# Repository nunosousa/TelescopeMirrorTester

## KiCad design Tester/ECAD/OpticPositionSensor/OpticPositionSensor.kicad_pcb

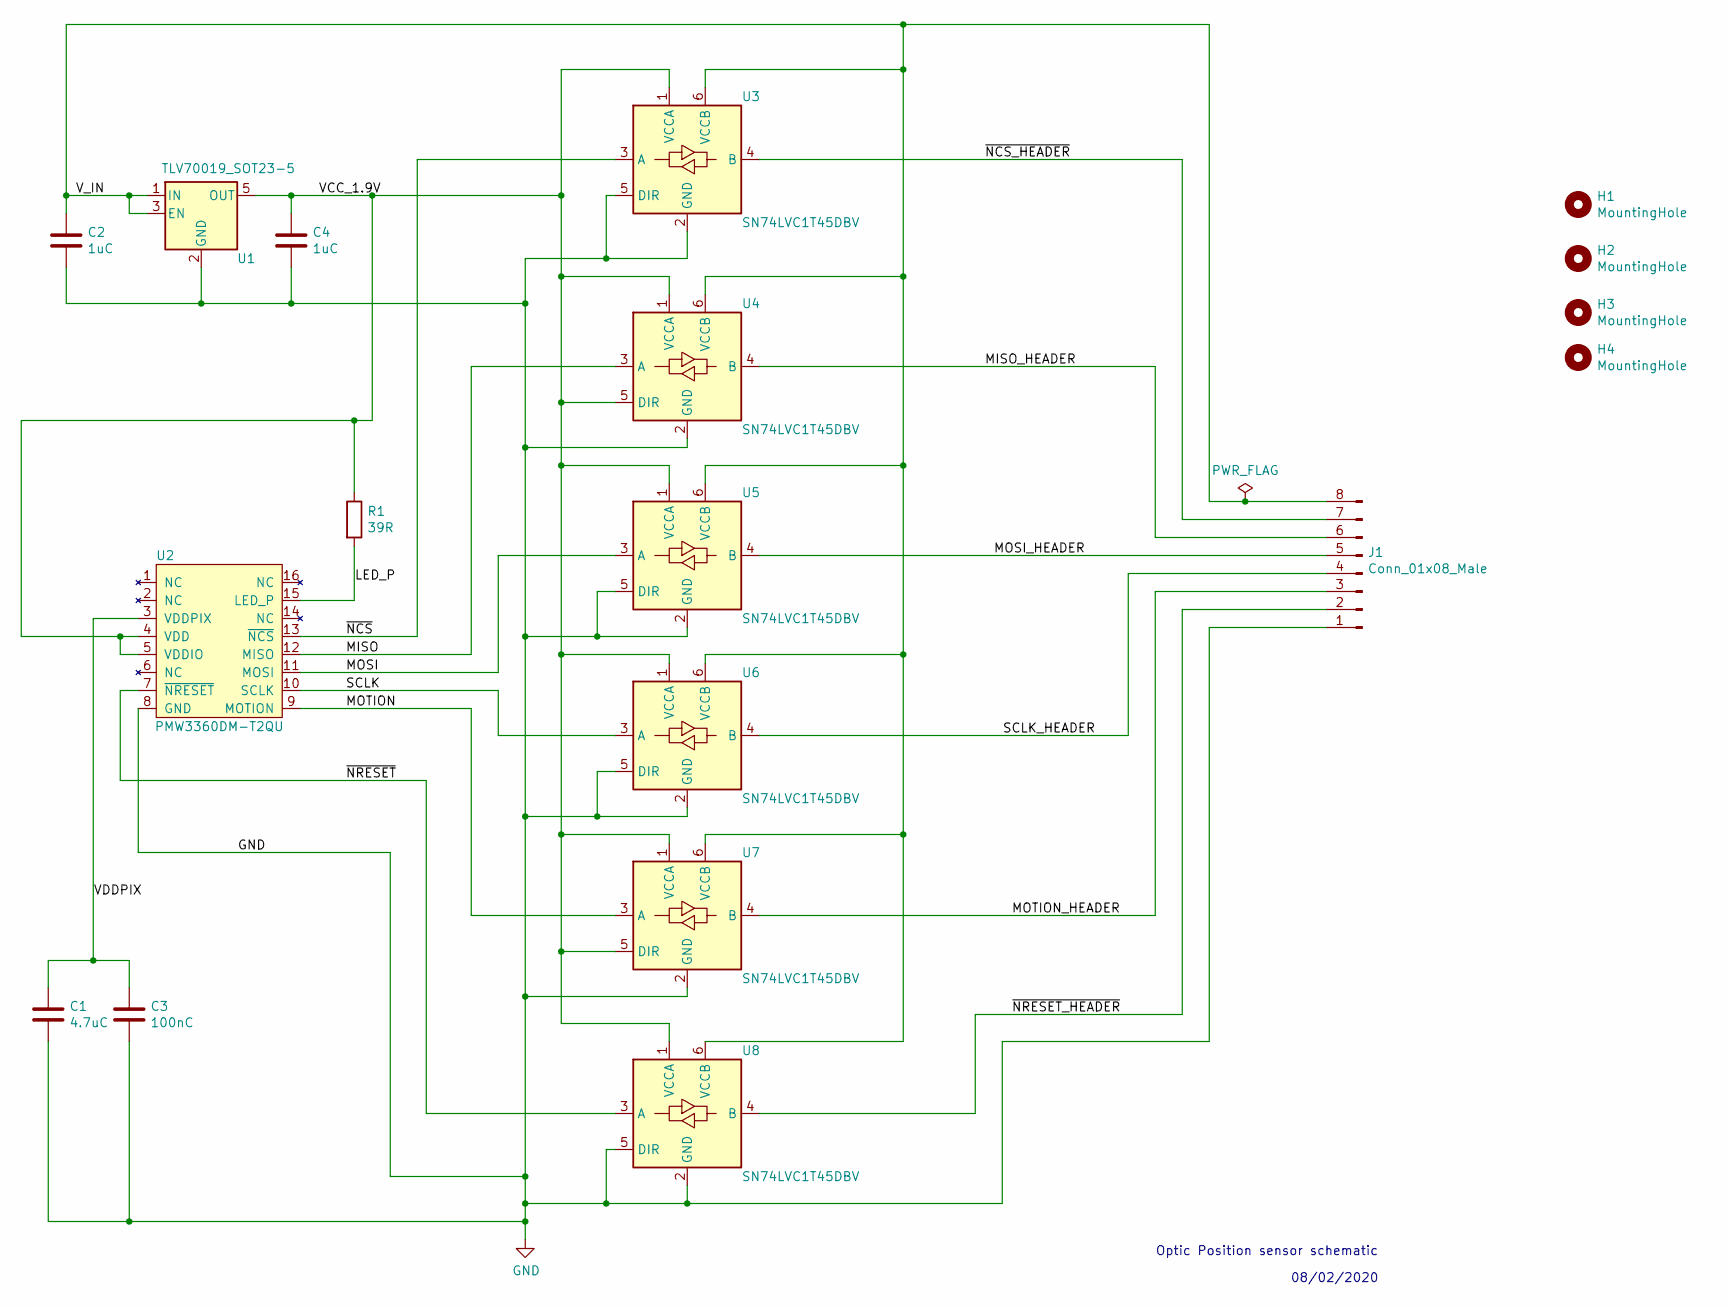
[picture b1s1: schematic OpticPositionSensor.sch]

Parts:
C1: 4.7uC; C_0805_2012Metric_Pad1.15x1.40mm_HandSolder; Manufacturer Part Number C0805C475K9PACTU
C2, C4: 1uC; C_0805_2012Metric_Pad1.15x1.40mm_HandSolder; Manufacturer Part Number CC0805MKX7R7BB105
C3: 100nC; C_0805_2012Metric_Pad1.15x1.40mm_HandSolder; Manufacturer Part Number CC0805ZRY5V8BB104
H1, H2, H3, H4: MountingHole; MountingHole_3.2mm_M3_Pad
J1: Conn_01x08_Male; Molex_PicoBlade_53048-0810_1x08_P1.25mm_Horizontal; Manufacturer Part Number 0530480810
R1: 39R; R_0805_2012Metric_Pad1.15x1.40mm_HandSolder; Manufacturer Part Number RC0805FR-0739RL
U1: TLV70019_SOT23-5; SOT-23-5_HandSoldering; Manufacturer Part Number TLV70019DDCT
U2: PMW3360DM-T2QU
U3, U4, U5, U6, U7, U8: SN74LVC1T45DBV; SOT-23-6_Handsoldering; Manufacturer Part Number SN74LVC1T45DBVR

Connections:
/LED_P: R1.2, U2.15 (LED_P)
/MISO: U2.12 (MISO), U4.3 (A)
/MISO_HEADER: J1.6, U4.4 (B)
/MOSI: U2.11 (MOSI), U5.3 (A)
/MOSI_HEADER: J1.5, U5.4 (B)
/MOTION: U2.9 (MOTION), U7.3 (A)
/MOTION_HEADER: J1.3, U7.4 (B)
/SCLK: U2.10 (SCLK), U6.3 (A)
/SCLK_HEADER: J1.4, U6.4 (B)
/VCC_1.9V: C4.1, R1.1, U1.5 (OUT), U2.4 (VDD), U2.5 (VDDIO), U3.1 (VCCA), U4.1 (VCCA), U4.5 (DIR), U5.1 (VCCA), U6.1 (VCCA), U7.1 (VCCA), U7.5 (DIR), U8.1 (VCCA)
/VDDPIX: C1.1, C3.1, U2.3 (VDDPIX)
/V_IN: C2.1, J1.8, U1.1 (IN), U1.3 (EN), U3.6 (VCCB), U4.6 (VCCB), U5.6 (VCCB), U6.6 (VCCB), U7.6 (VCCB), U8.6 (VCCB)
/~NCS: U2.13 (~NCS), U3.3 (A)
/~NCS_HEADER: J1.7, U3.4 (B)
/~NRESET: U2.7 (~NRESET), U8.3 (A)
/~NRESET_HEADER: J1.2, U8.4 (B)
GND: C1.2, C2.2, C3.2, C4.2, J1.1, U1.2 (GND), U2.8 (GND), U3.2 (GND), U3.5 (DIR), U4.2 (GND), U5.2 (GND), U5.5 (DIR), U6.2 (GND), U6.5 (DIR), U7.2 (GND), U8.2 (GND), U8.5 (DIR)

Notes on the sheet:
08/02/2020
Optic Position sensor schematic

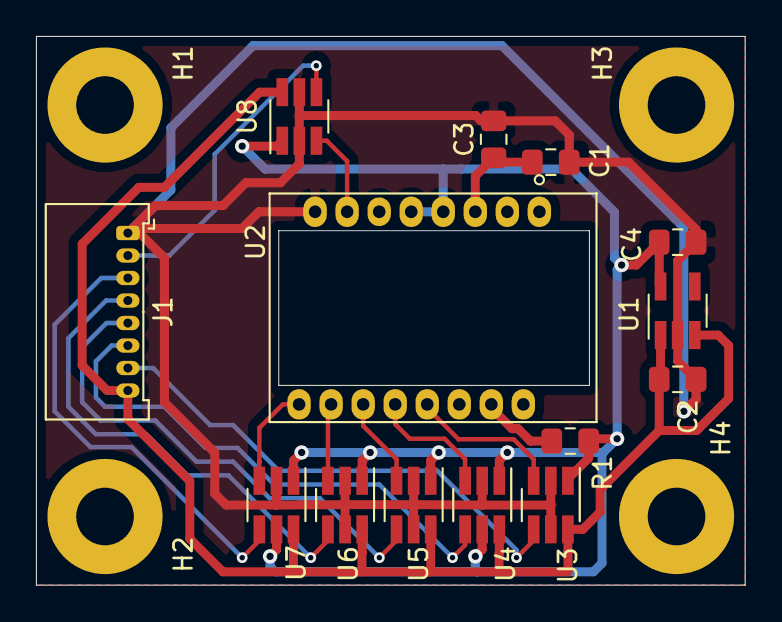
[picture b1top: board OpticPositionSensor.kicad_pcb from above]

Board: 2 copper layers, 39.4 x 30.5 mm, 18 parts (0 on the bottom side), 17 nets.

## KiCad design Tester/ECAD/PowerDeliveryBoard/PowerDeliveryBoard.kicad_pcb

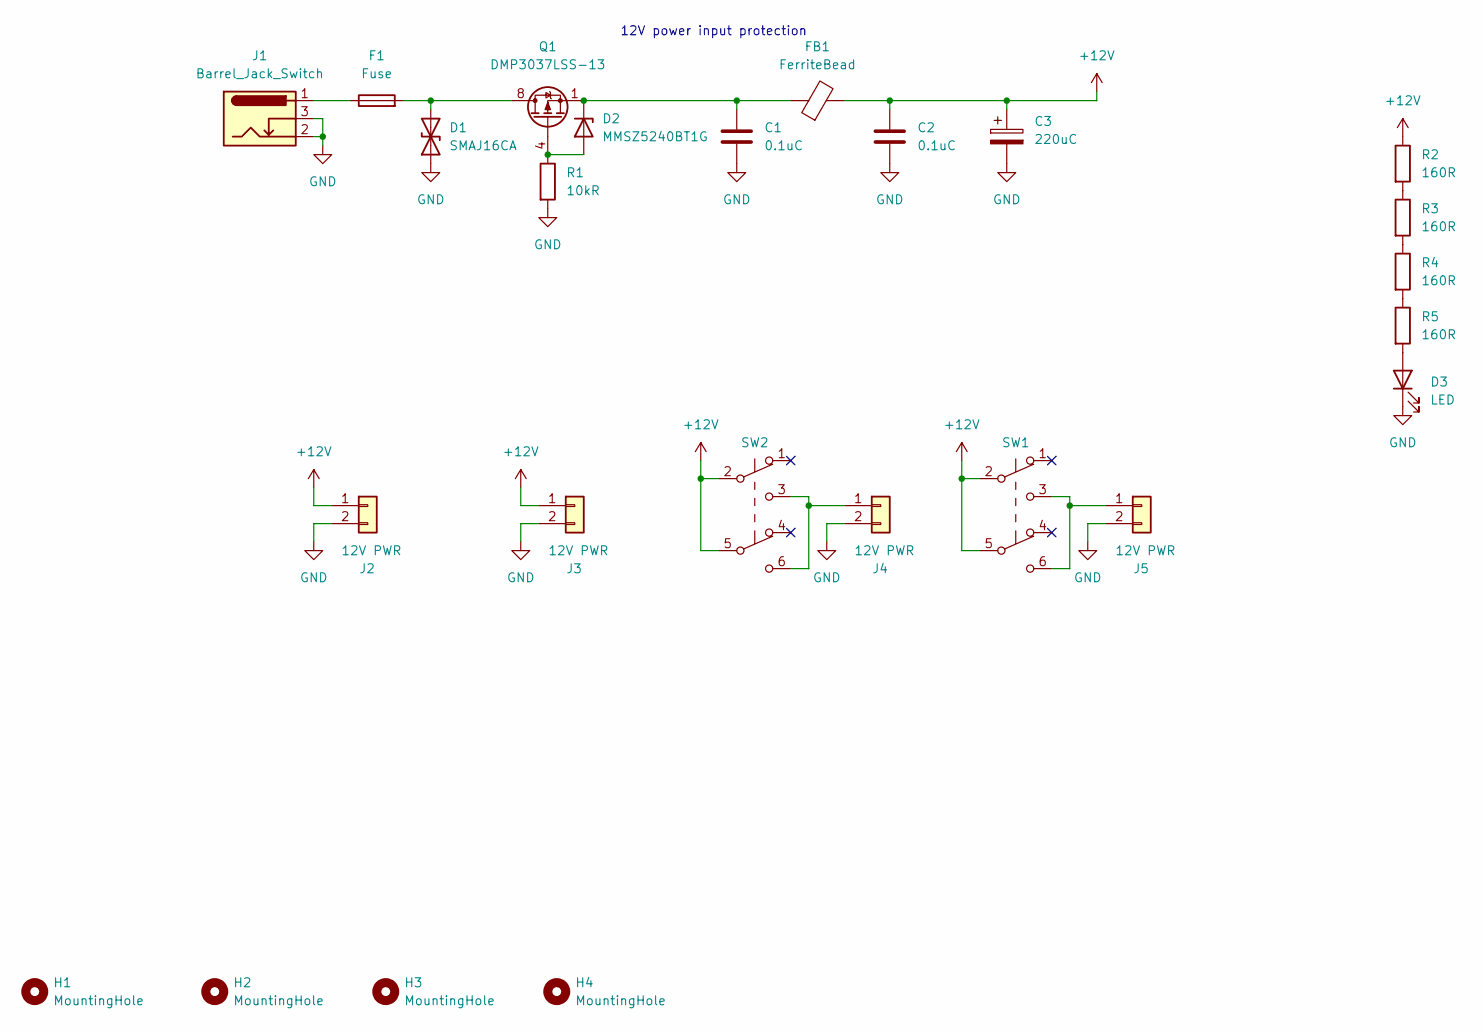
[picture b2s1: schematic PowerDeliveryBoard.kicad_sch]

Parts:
C1, C2: 0.1uC; C_0805_2012Metric_Pad1.18x1.45mm_HandSolder; MPN CL21B104KBCNNNC
C3: 220uC; CP_Radial_D8.0mm_P3.50mm; MPN 25YXF220MEFC8X11.5
D1: SMAJ16CA; D_SMA; MPN SMAJ16CA-13-F
D2: MMSZ5240BT1G; D_SOD-123; MPN MMSZ5240BT1G
D3: LED; D_0805_2012Metric_Pad1.15x1.40mm_HandSolder; MPN 17-21SYGC/S530-E3/TR8
F1: Fuse; Fuseholder_Cylinder-5x20mm_Stelvio-Kontek_PTF78_Horizontal_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; MPN PTF-77
FB1: FerriteBead; L_1806_4516Metric; MPN BLM41PG600SN1L
H1, H2, H3, H4: MountingHole; MountingHole_5.3mm_M5; MPN N/A
J1: Barrel_Jack_Switch; BarrelJack_DC-042C-W-2.5_Horizontal; MPN DC-042C-W-2.5
J2, J3, J4, J5: 12V PWR; HC-2510-2A; MPN HC-2510-2A
Q1: DMP3037LSS-13; SOIC-8_3.9x4.9mm_P1.27mm; MPN DMP3037LSS-13
R1: 10kR; R_0805_2012Metric_Pad1.20x1.40mm_HandSolder; MPN RC0805FR-0710KL
R2, R3, R4, R5: 160R; R_0805_2012Metric_Pad1.20x1.40mm_HandSolder; MPN AC0805FR-7W160RL
SW1, SW2: SW_Push_DPDT; SW_Push_2P2T_Toggle_Generic_5_8_x_5_8; MPN PB22E60L

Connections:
+12V: C2.2, C3.1, FB1.2, J2.1, J3.1, R2.1, SW1.2 (B), SW1.5 (B), SW2.2 (B), SW2.5 (B)
GND: C1.1, C2.1, C3.2, D1.1 (A1), D3.1 (K), J1.2, J1.3, J2.2, J3.2, J4.2, J5.2, R1.2
unnamed: C1.2, D2.1 (K), FB1.1, Q1.1 (S), Q1.2 (S), Q1.3 (S)
unnamed: D1.2 (A2), F1.2, Q1.5 (D), Q1.6 (D), Q1.7 (D), Q1.8 (D)
unnamed: D2.2 (A), Q1.4 (G), R1.1
unnamed: D3.2 (A), R5.2
unnamed: F1.1, J1.1
unnamed: J4.1, SW2.3 (C), SW2.6 (C)
unnamed: J5.1, SW1.3 (C), SW1.6 (C)
unnamed: R2.2, R3.1
unnamed: R3.2, R4.1
unnamed: R4.2, R5.1

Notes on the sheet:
12V power input protection

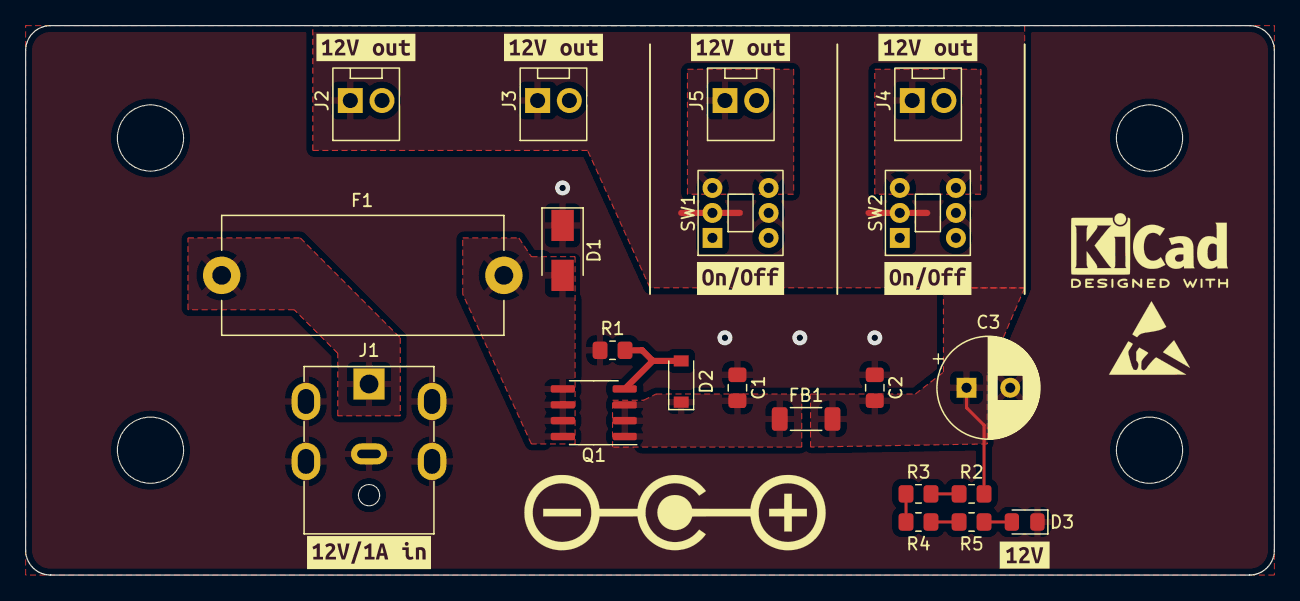
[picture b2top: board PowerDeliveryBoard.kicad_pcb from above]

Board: 2 copper layers, 100.0 x 44.0 mm, 33 parts (0 on the bottom side), 12 nets.

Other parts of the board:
kibuzzard-6388F516: G***; kibuzzard-6388F516
kibuzzard-63891CDB: G***; kibuzzard-63891CDB
kibuzzard-638910D3, kibuzzard-638910D3#2: G***; kibuzzard-638910D3
kibuzzard-638911E5: G***; kibuzzard-638911E5
kibuzzard-638911EA: G***; kibuzzard-638911EA
kibuzzard-6389104C, kibuzzard-6389104C#2: G***; kibuzzard-6389104C

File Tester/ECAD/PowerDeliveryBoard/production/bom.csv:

Designator,Footprint,Quantity,Value,LCSC Part #
"C1, C2",C_0805_2012Metric_Pad1.18x1.45mm_HandSolder,2,0.1uC,CL21B104KBCNNNC
C3,CP_Radial_D8.0mm_P3.50mm,1,220uC,25YXF220MEFC8X11.5
D1,D_SMA,1,SMAJ16CA,SMAJ16CA-13-F
D2,D_SOD-123,1,MMSZ5240BT1G,MMSZ5240BT1G
D3,D_0805_2012Metric_Pad1.15x1.40mm_HandSolder,1,LED,17-21SYGC/S530-E3/TR8
F1,Fuseholder_Cylinder-5x20mm_Stelvio-Kontek_PTF78_Horizontal_Open,1,Fuse,PTF-77
FB1,L_1806_4516Metric,1,FerriteBead,BLM41PG600SN1L
J1,BarrelJack_DC-042C-W-2.5_Horizontal,1,Barrel_Jack_Switch,DC-042C-W-2.5
"J2, J3, J4, J5",HC-2510-2A,4,12V PWR,HC-2510-2A
Q1,SOIC-8_3.9x4.9mm_P1.27mm,1,DMP3037LSS-13,DMP3037LSS-13
R1,R_0805_2012Metric_Pad1.20x1.40mm_HandSolder,1,10kR,RC0805FR-0710KL
R2,R_0805_2012Metric_Pad1.20x1.40mm_HandSolder,1,1kR,AC0805FR-7W1KL
"SW1, SW2",SW_Push_2P2T_Toggle_Generic_5_8_x_5_8,2,SW_Push_DPDT,PB22E60L

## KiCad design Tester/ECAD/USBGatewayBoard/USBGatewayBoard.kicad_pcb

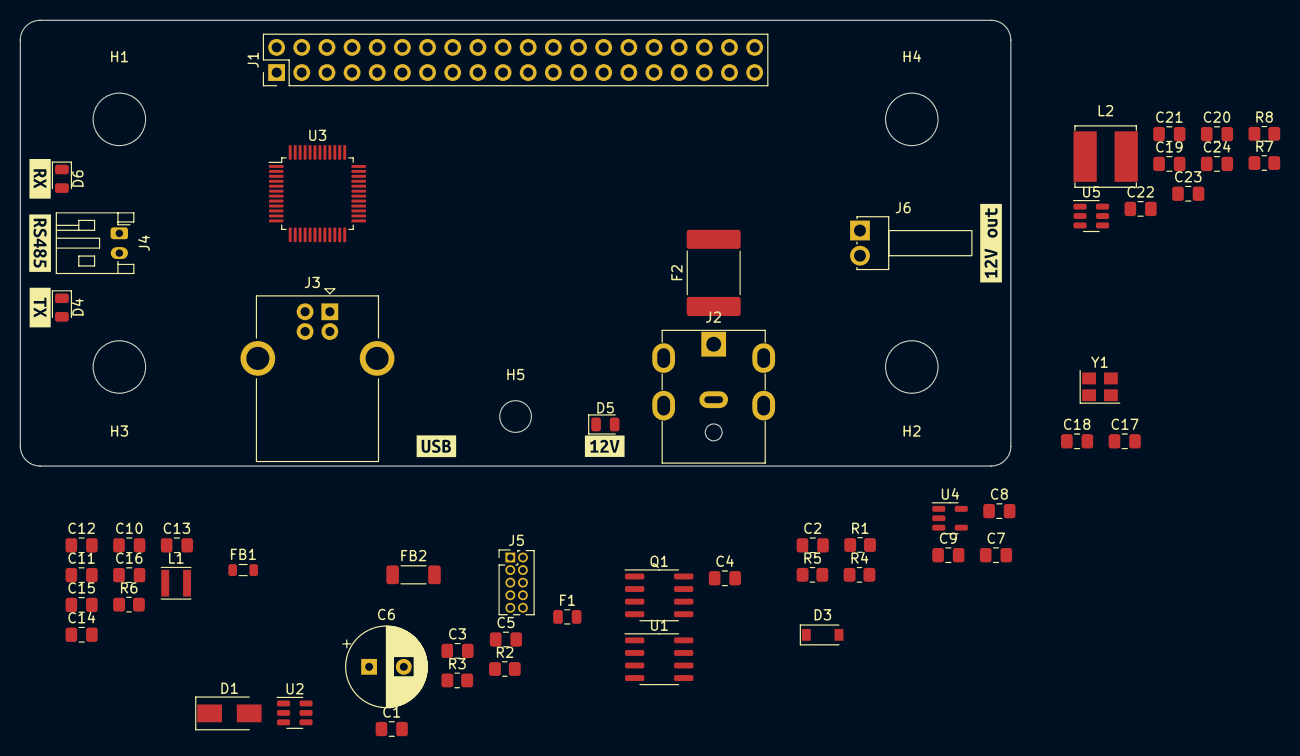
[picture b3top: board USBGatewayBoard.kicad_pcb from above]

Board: 2 copper layers, 100.0 x 45.0 mm, 67 parts (0 on the bottom side), 29 nets, no tracks yet.

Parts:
C1, C2, C3, C4, C5, C9, C12, C13, C16, C21, C22: 0.1uC; C_0805_2012Metric_Pad1.18x1.45mm_HandSolder
C6: 220uC; CP_Radial_D8.0mm_P3.50mm
C7, C8, C11: 1uC; C_0805_2012Metric_Pad1.18x1.45mm_HandSolder
C10: 4.7nC; C_0805_2012Metric_Pad1.18x1.45mm_HandSolder
C14, C15, C19, C20: 10uC; C_0805_2012Metric_Pad1.18x1.45mm_HandSolder
C17, C18: 5pC; C_0805_2012Metric_Pad1.18x1.45mm_HandSolder
C23, C24: 22uC; C_0805_2012Metric_Pad1.18x1.45mm_HandSolder
D1: SMAJ16CA; D_SMA
D3: MMSZ5240BT1G; D_SOD-123
D4, D5, D6: LED; LED_0805_2012Metric
F1: Polyfuse; Fuse_0805_2012Metric
F2: Polyfuse; Fuse_2920_7451Metric
FB1: 220Ω@100MHz; L_0805_2012Metric
FB2: FerriteBead; L_1806_4516Metric
H1, H2, H3, H4: MountingHole; MountingHole_5.3mm_M5
H5: MountingHole; MountingHole_3.2mm_M3
J1: Conn_02x20_Odd_Even; PinHeader_2x20_P2.54mm_Vertical
J2: Barrel_Jack_Switch; BarrelJack_DC-042C-W-2.5_Horizontal
J3: USB_B; USB_B_OST_USB-B1HSxx_Horizontal
J4: RS485; JST_PH_S2B-PH-K_1x02_P2.00mm_Horizontal
J5: Conn_SWD_10; PinHeader_2x05_P1.27mm_Vertical
J6: 12V PWR; HC-2510-2AW
L1: 10uL; L_Taiyo-Yuden_MD-3030
L2: 3.3uL; L_Bourns_SRN6045TA
Q1: DMP3037LSS-13; SOIC-8_3.9x4.9mm_P1.27mm
R1: 120R; R_0805_2012Metric_Pad1.20x1.40mm_HandSolder
R2, R3, R5, R7: 10kR; R_0805_2012Metric_Pad1.20x1.40mm_HandSolder
R4: 1kR; R_0805_2012Metric_Pad1.20x1.40mm_HandSolder
R6: 1MR; R_0805_2012Metric_Pad1.20x1.40mm_HandSolder
R8: 54.9kR; R_0805_2012Metric_Pad1.20x1.40mm_HandSolder
U1: SP3485; SOIC-8_3.9x4.9mm_P1.27mm
U2: USBLC6-2SC6; SOT-23-6
U3: ATSAMD21G18A-A; TQFP-48_7x7mm_P0.5mm
U4: TLV70033DDCT; SOT-23-5
U5: TPS563201; SOT-23-6
Y1: 12MHz; Crystal_SMD_3225-4Pin_3.2x2.5mm
kibuzzard-636F7E30: G***; kibuzzard-636F7E30
kibuzzard-636F7E53: G***; kibuzzard-636F7E53
kibuzzard-636FE58E: G***; kibuzzard-636FE58E
kibuzzard-636FE59D: G***; kibuzzard-636FE59D
kibuzzard-6370312D: G***; kibuzzard-6370312D
kibuzzard-63703123: G***; kibuzzard-63703123

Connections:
+3.3V: C1.2, C8.2, J5.1 (VTref), L1.1, R4.1, R5.1, U1.8 (VCC), U4.5 (OUT)
+5V: C7.2, C23.1, C24.1, L2.2, R8.2, U4.1 (IN), U4.3 (EN)
+12V: C5.2, C6.1, C19.1, C20.1, C21.1, FB2.2, J6.1, U5.3 (VIN), U5.5 (EN)
/RS485_DIR: R2.1, U1.2 (~RE), U1.3 (DE)
/SWCLK: J5.4 (SWDCLK/TCK), R4.2, U3.45 (PA30)
/SWDIO: J5.2 (SWDIO/TMS), U3.46 (PA31)
/USB_D+: U2.4 (I/O2), U3.34 (PA25)
/USB_D-: U2.6 (I/O1), U3.33 (PA24)
/VDD: C9.2, C12.2, C13.2, C14.2, FB1.1, L1.2, U3.17 (VDDIO), U3.36 (VDDIO), U3.44 (VDDIN)
/VDDANA: C15.2, C16.2, FB1.2, U3.6 (VDDANA)
/VDDCORE: C11.2, U3.43 (VDDCORE)
/XIN: C18.1, U3.23 (PA14), Y1.3
/XOUT: C17.1, U3.24 (PA15), Y1.1
/~RESET: C2.2, J5.10 (~RESET), R5.2, U3.40 (~RESET)
GND: C1.1, C2.1, C3.1, C4.1, C5.1, C6.2, C7.1, C8.1, C9.1, C10.1, C11.1, C12.1, C13.1, C14.1, C15.1, C16.1, C17.2, C18.2, C19.2, C20.2, C21.2, C23.2, C24.2, D1.1 (A1), J1.2, J1.4, J1.6, J1.8, J1.10, J1.12, J1.14, J1.16, J1.18, J1.20, J1.22, J1.24, J1.26, J1.28, J1.30, J1.32, J1.34, J1.36, J1.38, J1.40, J2.2, J2.3, J3.4 (GND), J5.3 (GND), J5.5 (GND), J6.2, R2.2, R3.2, R6.2, R7.2, U1.5 (GND), U2.2 (GND), U3.5 (GNDANA), U3.18 (GND), U3.35 (GND), U3.42 (GND), U4.2 (GND), U5.1 (GND), Y1.2, Y1.4
unnamed: C4.2, D3.1 (K), FB2.1, Q1.1 (S), Q1.2 (S), Q1.3 (S)
unnamed: C10.2, J3.5 (Shield), R6.1
unnamed: C22.1, U5.6 (VBST)
unnamed: C22.2, L2.1, U5.2 (SW)
unnamed: D1.2 (A2), F2.2, Q1.5 (D), Q1.6 (D), Q1.7 (D), Q1.8 (D)
unnamed: D3.2 (A), Q1.4 (G), R3.1
unnamed: F1.1, J3.1 (VBUS)
unnamed: F2.1, J2.1
unnamed: J3.2 (D-), U2.1 (I/O1)
unnamed: J3.3 (D+), U2.3 (I/O2)
unnamed: J4.1, R1.1, U1.7 (B)
unnamed: J4.2, R1.2, U1.6 (A)
unnamed: R7.1, R8.1, U5.4 (VFB)
VBUS: C3.2, F1.2, U2.5 (VBUS)

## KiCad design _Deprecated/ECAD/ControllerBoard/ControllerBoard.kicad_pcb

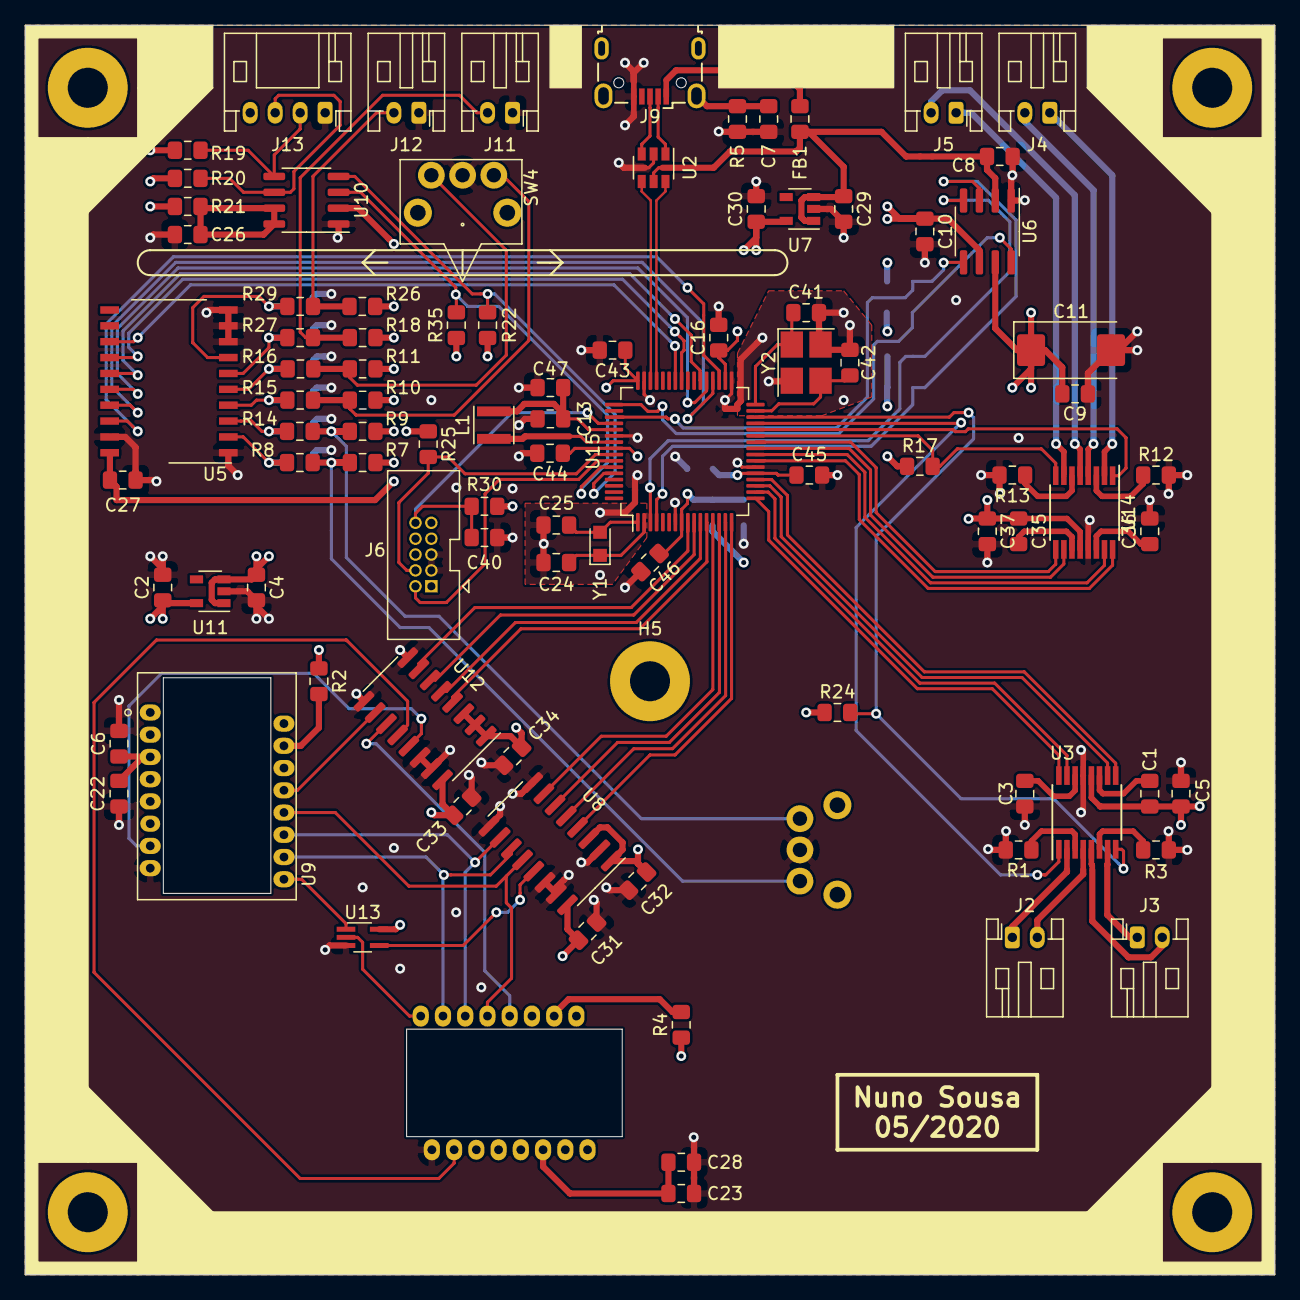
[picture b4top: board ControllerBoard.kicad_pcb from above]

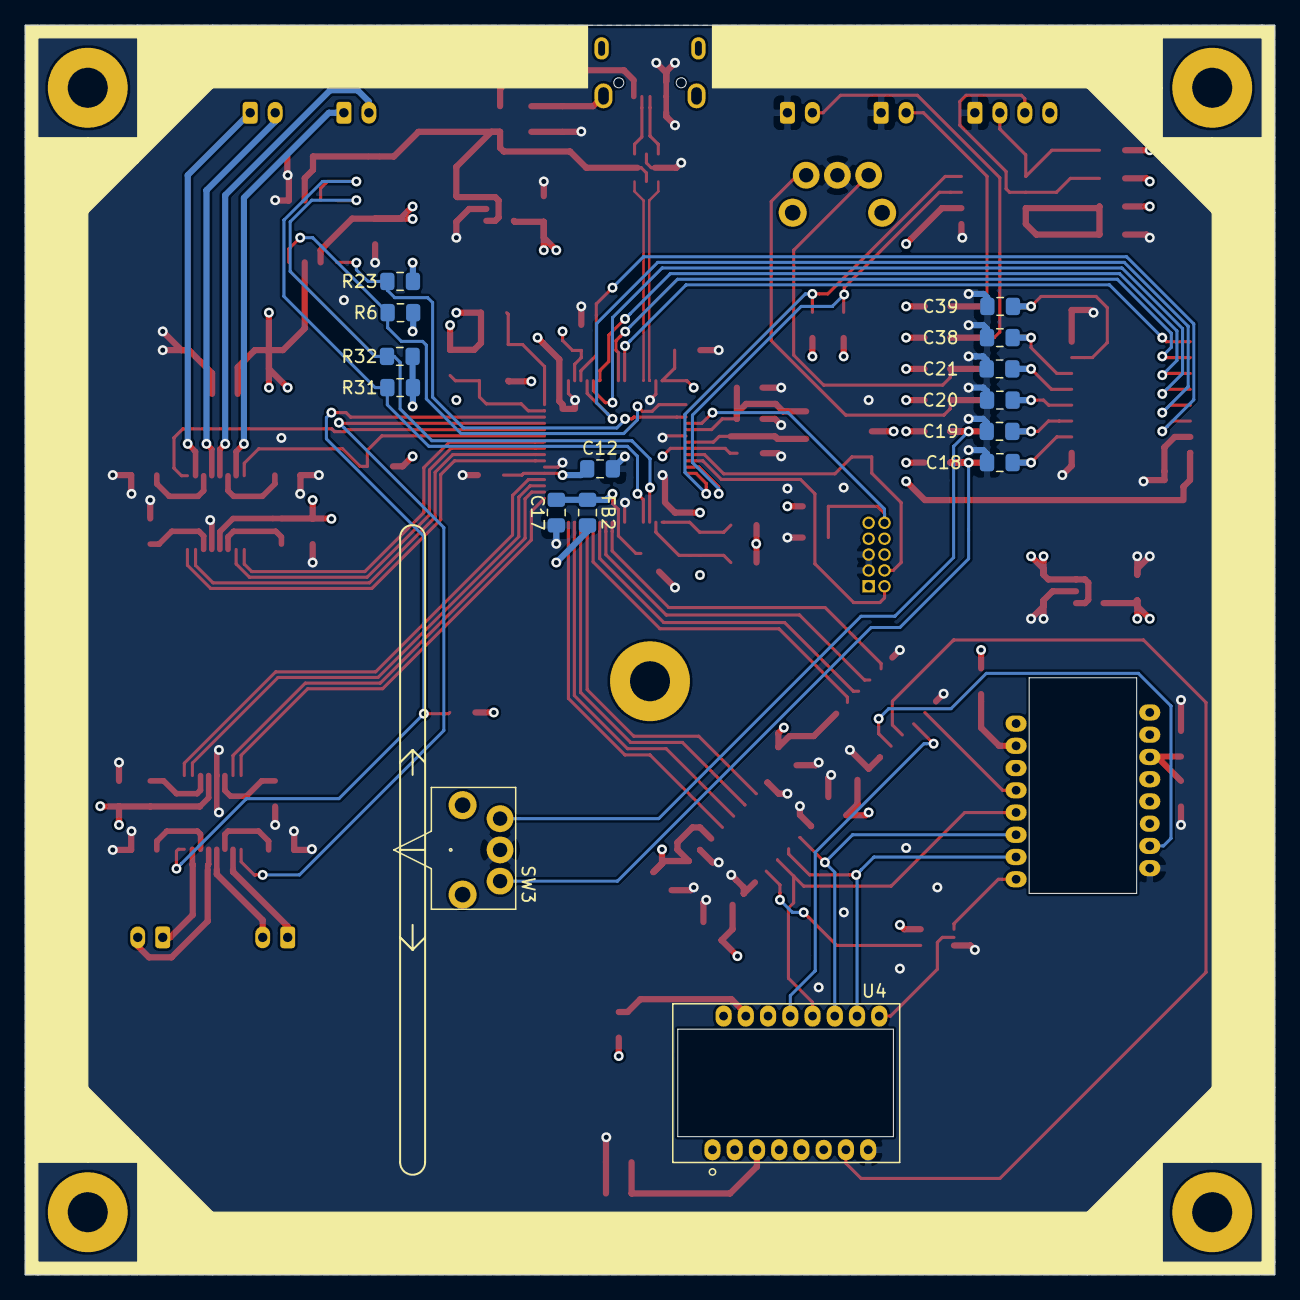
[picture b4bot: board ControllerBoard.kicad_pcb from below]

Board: 4 copper layers, 100.0 x 100.0 mm, 116 parts (15 on the bottom side), 103 nets.

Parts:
C1, C35: 0.01uC; C_0805_2012Metric_Pad1.15x1.40mm_HandSolder
C2, C4, C29, C30: 1uC; C_0805_2012Metric_Pad1.15x1.40mm_HandSolder
C3, C36: 2.2uC; C_0805_2012Metric_Pad1.15x1.40mm_HandSolder
C5, C12, C17, C37: 10uC; C_0805_2012Metric_Pad1.15x1.40mm_HandSolder
C6, C23, C40, C47: 4.7uC; C_0805_2012Metric_Pad1.15x1.40mm_HandSolder
C7: 4.7nC; C_0805_2012Metric_Pad1.15x1.40mm_HandSolder
C8, C9, C10, C13, C16, C18, C19, C20, C21, C22, C26, C27, C28, C31, C32, C33, C34, C38, C39, C43, C44, C45, C46: 0.1uC; C_0805_2012Metric_Pad1.15x1.40mm_HandSolder
C11: 150uCP; CP_EIA-7343-31_Kemet-D_Pad2.25x2.55mm_HandSolder
C24, C25: 6.8pC; C_0805_2012Metric_Pad1.15x1.40mm_HandSolder
C41, C42: 5pC; C_0805_2012Metric_Pad1.15x1.40mm_HandSolder
FB1, FB2: Ferrite_Bead; L_0805_2012Metric_Pad1.15x1.40mm_HandSolder
H1, H2, H3, H4, H5: MountingHole; MountingHole_3.2mm_M3_Pad
J2, J3, J4, J5, J11, J12: Conn_01x02; JST_PH_S2B-PH-K_1x02_P2.00mm_Horizontal
J6: Conn_ARM_JTAG_SWD_10; PinHeader_2x05_P1.27mm_Vertical
J9: USB_B_Micro; USB_Micro-B_Wuerth_629105150521
J13: Conn_01x04; JST_PH_S4B-PH-K_1x04_P2.00mm_Horizontal
L1: 10uL; L_Taiyo-Yuden_MD-3030
NT1, NT2, NT4, NT5: Net-Tie_2; NetTie-2_SMD_Pad0.5mm
R1, R3, R12, R13: 1R; R_0805_2012Metric_Pad1.15x1.40mm_HandSolder
R2, R4: 39R; R_0805_2012Metric_Pad1.15x1.40mm_HandSolder
R5: 1MR; R_0805_2012Metric_Pad1.15x1.40mm_HandSolder
R6, R7, R8, R9, R10, R11, R14, R15, R16, R17, R18, R23, R24, R26, R27, R29, R31, R32: 10kR; R_0805_2012Metric_Pad1.15x1.40mm_HandSolder
R19, R20, R22, R35: 4.7kR; R_0805_2012Metric_Pad1.15x1.40mm_HandSolder
R21: 200kR; R_0805_2012Metric_Pad1.15x1.40mm_HandSolder
R25: 1kR; R_0805_2012Metric_Pad1.15x1.40mm_HandSolder
R30: 100kR; R_0805_2012Metric_Pad1.15x1.40mm_HandSolder
SW3, SW4: SW_SPDT_MSM; ESE24SH1
U2: USBLC6-2SC6; SOT-23-6
U3, U14: DRV8833PW; TSSOP-16_4.4x5mm_P0.65mm
U4, U9: PMW3360DM-T2QU
U5: 74HC7541; SO-20_12.8x7.5mm_P1.27mm
U6: TPS2046B; SOIC-8_3.9x4.9mm_P1.27mm
U7: TLV70033_SOT23-5; SOT-23-5
U8, U12: SN74AVC4T245PW; SOIC-16_3.9x9.9mm_P1.27mm
U10: PCA9306; SO-8_3.9x4.9mm_P1.27mm
U11: TLV70019_SOT23-5; SOT-23-5
U13: 74LVC1G08; SOT-353_SC-70-5_Handsoldering
U15: ATSAMD51J18A-A; TQFP-64_10x10mm_P0.5mm
Y1: 32.768kHz; Crystal_SMD_2012-2Pin_2.0x1.2mm_HandSoldering
Y2: 12MHz; Crystal_SMD_3225-4Pin_3.2x2.5mm_HandSoldering

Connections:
/MCU/END_STOP_X+: U5.18, U15.35
/MCU/END_STOP_X-: U5.17, U15.36
/MCU/END_STOP_Y+: U5.16, U15.37
/MCU/END_STOP_Y-: U5.15, U15.38
/MCU/END_STOP_Z+: U5.14, U15.41
/MCU/END_STOP_Z-: U5.13, U15.42
/MCU/GNDANA_1: C41.2, C42.2, NT1.1, Y2.2, Y2.4
/MCU/GNDANA_2: C24.2, C25.2, NT2.1
/MCU/LASER_SCL: R35.2, U10.3, U15.59
/MCU/LASER_SDA: R22.2, U10.4, U15.60
/MCU/MOTOR_CTRL_1A: U3.16, U15.17
/MCU/MOTOR_CTRL_1B: U3.15, U15.18
/MCU/MOTOR_CTRL_2A: U3.9, U15.20
/MCU/MOTOR_CTRL_2B: U3.10, U15.19
/MCU/MOTOR_CTRL_3A: U14.16, U15.23
/MCU/MOTOR_CTRL_3B: U14.15, U15.24
/MCU/MOTOR_CTRL_4A: U14.9, U15.26
/MCU/MOTOR_CTRL_4B: U14.10, U15.25
/MCU/MOTOR_FAULT_12: R24.2, U3.8, U15.30
/MCU/MOTOR_FAULT_34: R17.2, U14.8, U15.27
/MCU/MOTOR_SLEEP_12: U3.1, U15.29
/MCU/MOTOR_SLEEP_34: U14.1, U15.28
/MCU/POS_MISO: U8.5, U15.15
/MCU/POS_MOSI: U8.7, U15.13
/MCU/POS_MOTION: U8.4, U15.16
/MCU/POS_SCLK: U8.6, U15.14
/MCU/SWCLK: J6.4, R25.2, U15.57
/MCU/SWDIO: J6.2, U15.58
/MCU/USB_D+: U2.4, U15.46
/MCU/USB_D-: U2.6, U15.45
/MCU/V3_3: C12.1, C16.1, C30.1, C32.1, C34.1, C43.1, C44.1, C45.1, FB2.2, J6.1, NT4.1, R6.1, R7.1, R9.1, R10.1, R11.1, R17.1, R18.1, R22.1, R23.1, R24.1, R25.1, R26.1, R30.1, R31.1, R32.1, R35.1, U7.5, U8.1, U8.3, U10.2, U12.1, U12.2, U12.3, U15.21, U15.34, U15.48, U15.56
/MCU/VDDANA: C17.1, C46.1, FB2.1, U15.8
/MCU/VDDCORE: C13.1, C47.1, L1.2, U15.53
/MCU/VSW: L1.1, U15.55
/MCU/XIN: C42.1, U15.31, Y2.3
/MCU/XIN32: C25.1, U15.1, Y1.2
/MCU/XOUT: C41.1, U15.32, Y2.1
/MCU/XOUT32: C24.1, U15.2, Y1.1
/MCU/~POS1_NCS: U12.7, U15.9
/MCU/~POS1_NRESET: U12.4, U15.12
/MCU/~POS2_NCS: U12.6, U15.10
/MCU/~POS2_NRESET: U12.5, U15.11
/MCU/~RESET: C40.1, J6.10, R30.2, U15.52
/Motor Control/V5_0: C1.1, C5.1, C9.1, C11.1, C35.1, C37.1, U3.12, U6.7, U14.12
/Position Sensor/V5_0: C4.1, C10.1, J13.4, R19.1, R20.1, R21.1, U6.6, U11.1, U11.3
/Power/LOAD_OVERCURRENT_DIGITAL_LOGIC: R23.2, U6.5, U15.51
/Power/LOAD_OVERCURRENT_MOTOR: R6.2, U6.8, U15.49
/Power/V5_USB: C29.1, FB1.1, NT5.1, U2.5, U7.1, U7.3
/Power/~POWER_SWITCH_ANALOGUE_LOADS: R31.2, U6.3, U15.4
/Power/~POWER_SWITCH_DIGITAL_LOGIC: R32.2, U6.4, U15.3
/USB Interface/D+: J9.3, U2.3
/USB Interface/D-: J9.2, U2.1
/USB Interface/SHIELD: C7.1, J9.6, R5.1
/USB Interface/VBUS: FB1.2, J9.1
GND: C2.2, C3.2, C4.2, C5.2, C6.2, C7.2, C8.2, C9.2, C10.2, C11.2, C12.2, C13.2, C16.2, C17.2, C18.2, C19.2, C20.2, C21.2, C22.2, C23.2, C26.2, C27.2, C28.2, C29.2, C30.2, C31.2, C32.2, C33.2, C34.2, C36.2, C37.2, C38.2, C39.2, C40.2, C43.2, C44.2, C45.2, C46.2, C47.2, J6.3, J6.5, J9.5, J11.1, J12.1, J13.1, NT1.2, NT2.2, R1.2, R3.2, R5.2, R12.2, R13.2, SW3.2, SW4.2, U2.2, U3.13, U4.8, U5.1, U5.8, U5.9, U5.10, U5.19, U6.1, U7.2, U8.2, U8.8, U8.9, U8.14, U8.15, U9.8, U10.1, U11.2, U12.8, U12.9, U12.14, U12.15, U13.3, U14.13, U15.7, U15.22, U15.33, U15.47, U15.54
unnamed: C1.2, U3.11
unnamed: C3.1, U3.14
unnamed: C8.1, NT5.2, U6.2
unnamed: C18.1, R8.1, U5.2
unnamed: C19.1, R14.1, U5.3
unnamed: C20.1, R15.1, U5.4
unnamed: C21.1, R16.1, U5.5
unnamed: C6.1, C22.1, U9.3
unnamed: C23.1, C28.1, U4.3
unnamed: C26.1, R21.2, U10.7, U10.8
unnamed: C27.1, NT4.2, U5.20
unnamed: C35.2, U14.11
unnamed: C36.1, U14.14
unnamed: C38.1, R27.1, U5.6
unnamed: C39.1, R29.1, U5.7
unnamed: J2.1, U3.2
unnamed: J2.2, U3.4
unnamed: J3.1, U3.7
unnamed: J3.2, U3.5
unnamed: J4.1, U14.2
unnamed: J4.2, U14.4
unnamed: J5.1, U14.7
unnamed: J5.2, U14.5
unnamed: J11.2, R18.2, R27.2
unnamed: J12.2, R26.2, R29.2
unnamed: J13.2, R19.2, U10.5
unnamed: J13.3, R20.2, U10.6
unnamed: R1.1, U3.3
unnamed: R2.2, U9.15
unnamed: R3.1, U3.6
unnamed: R4.2, U4.15
unnamed: R7.2, R8.2, SW3.1
unnamed: R10.2, R15.2, SW4.1
unnamed: R11.2, R16.2, SW4.3
unnamed: R12.1, U14.3
unnamed: R13.1, U14.6
unnamed: R9.2, R14.2, SW3.3
unnamed: U4.10, U8.11, U9.10
unnamed: U4.11, U8.10, U9.11
unnamed: U4.12, U8.12, U9.12
unnamed: U9.13, U12.10
unnamed: U4.13, U12.11
unnamed: U4.7, U12.12
unnamed: U9.7, U12.13
unnamed: U9.9, U13.1
unnamed: U4.9, U13.2
unnamed: U8.13, U13.4
VCC: C2.1, C31.1, C33.1, R2.1, R4.1, U4.4, U4.5, U8.16, U9.4, U9.5, U11.5, U12.16, U13.5

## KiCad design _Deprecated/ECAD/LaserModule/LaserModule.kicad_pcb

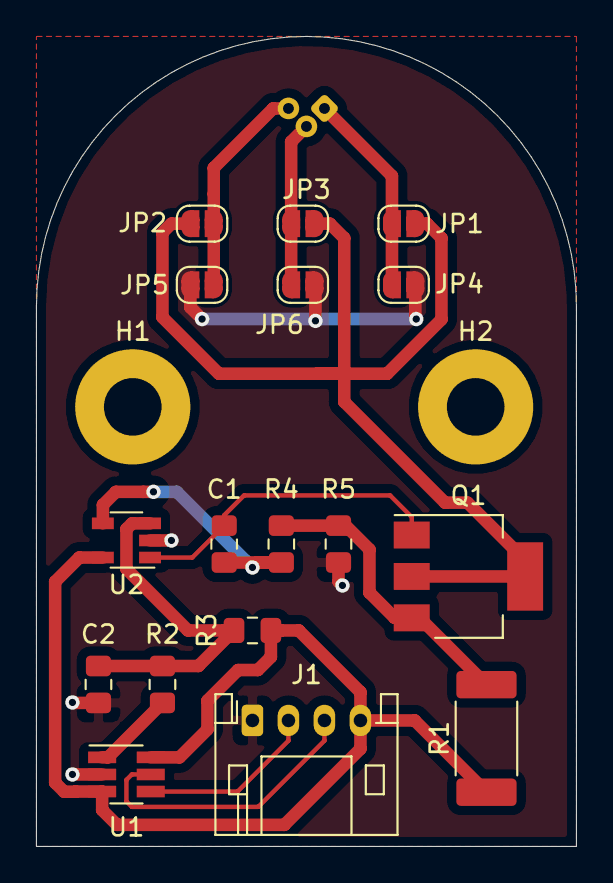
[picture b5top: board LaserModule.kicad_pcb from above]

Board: 2 copper layers, 30.0 x 45.0 mm, 20 parts (1 on the bottom side), 13 nets.

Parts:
C1: 100pC; C_0805_2012Metric_Pad1.15x1.40mm_HandSolder
C2: 1nC; C_0805_2012Metric_Pad1.15x1.40mm_HandSolder
H1, H2: MountingHole; MountingHole_3.2mm_M3_Pad
J1: Conn_01x04; JST_PH_S4B-PH-K_1x04_P2.00mm_Horizontal
JP1, JP2, JP3, JP4, JP5, JP6: SolderJumper_2_Open; SolderJumper-2_P1.3mm_Open_RoundedPad1.0x1.5mm
LD1: SLD3134VL; LaserDiode_TO18-D5.6-3
Q1: ZXMP6A17G; SOT-223-3_TabPin2
R1: 12R; R_2512_6332Metric_Pad1.52x3.35mm_HandSolder
R2: 20kR; R_0805_2012Metric_Pad1.15x1.40mm_HandSolder
R3: 30kR; R_0805_2012Metric_Pad1.15x1.40mm_HandSolder
R4: 10kR; R_0805_2012Metric_Pad1.15x1.40mm_HandSolder
R5: 4kR; R_0805_2012Metric_Pad1.15x1.40mm_HandSolder
U1: MCP4716; SOT-23-6_Handsoldering
U2: AD8601; TSOT-23-5

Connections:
+5C: J1.4, R1.1, R3.1, U1.3, U1.6, U2.5
/D: JP1.2, JP2.2, JP3.2, Q1.2
/G: C1.2, Q1.1, U2.1
/S: Q1.3, R1.2, R4.1, R5.1
/SCL: J1.3, U1.5
/SDA: J1.2, U1.4
/V+: C2.1, R2.2, R3.2, U2.3
/V-: C1.1, R4.2, U2.4
/VOUT: R2.1, U1.1
GND: C2.2, J1.1, JP4.1, JP5.1, JP6.1, R5.2, U1.2, U2.2
unnamed: JP1.1, JP4.2, LD1.1
unnamed: JP2.1, JP5.2, LD1.3
unnamed: JP3.1, JP6.2, LD1.2
